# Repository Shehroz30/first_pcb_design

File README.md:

# first_pcb_design
my first pcb design with a stm32f1 microcontroller

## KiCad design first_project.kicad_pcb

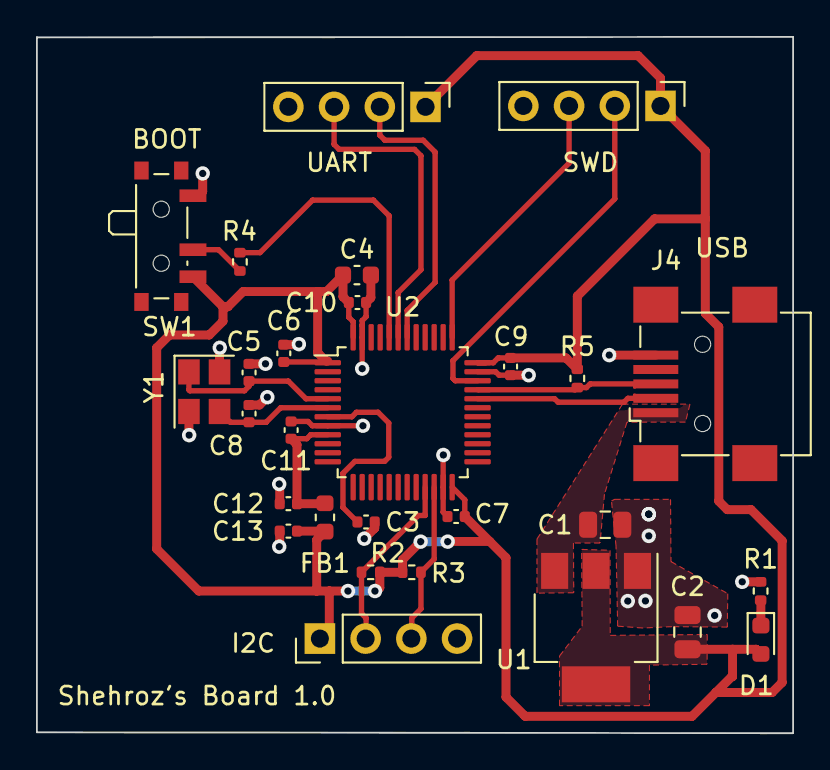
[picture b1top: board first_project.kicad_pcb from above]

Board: 2 copper layers, 42.0 x 38.7 mm, 28 parts (0 on the bottom side), 18 nets.

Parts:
C1, C2: 22u; C_0805_2012Metric
C3, C6, C7, C9, C10: 100n; C_0402_1005Metric
C4: 10u; C_0603_1608Metric
C5, C8: 10p; C_0402_1005Metric
C11: 10n; C_0402_1005Metric
C12, C13: 1u; C_0402_1005Metric
D1: RED; LED_0603_1608Metric
FB1: 120R; L_0603_1608Metric
J1, J2, J3: Conn_01x04_Male; PinHeader_1x04_P2.54mm_Vertical
J4: USB_B_Mini; USB_Mini-B_Wuerth_65100516121_Horizontal
R1, R2, R3, R5: 1k5; R_0402_1005Metric
R4: 10k; R_0402_1005Metric
SW1: SW_SPDT; SW_SPDT_PCM12
U1: AMS1117-3.3; SOT-223-3_TabPin2
U2: STM32F103C8T6; LQFP-48_7x7mm_P0.5mm
Y1: 16MHz; Crystal_SMD_3225-4Pin_3.2x2.5mm

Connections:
+3.3VA: C11.1, C12.1, FB1.2, U2.9
+3V3: C2.1, C4.1, C6.1, C7.1, C9.1, C10.1, C13.1, D1.2, FB1.1, J1.1, J2.1, J3.1, R2.1, R3.1, R5.1, SW1.3, U1.2, U2.1, U2.24, U2.36, U2.48
/HSE_IN: C5.1, U2.5, Y1.1
/HSE_OUT: C8.1, U2.6, Y1.3
/I2C2_SCL: J1.2, R2.2, U2.21
/I2C2_SDK: J1.3, R3.2, U2.22
/NRST: C3.1, U2.7
/SWCLK: J3.3, U2.37
/SWDIO: J3.2, U2.34
/USART1_RX: J2.3, U2.43
/USART1_TX: J2.2, U2.42
/USB_D+: J4.3, R5.2, U2.33
/USB_D-: J4.2, U2.32
GND: C1.2, C2.2, C3.2, C4.2, C5.2, C6.2, C7.2, C8.2, C9.2, C10.2, C11.2, C12.2, C13.2, J1.4, J2.4, J3.4, J4.5, R1.2, SW1.1, U1.1, U2.8, U2.23, U2.35, U2.47, Y1.2, Y1.4
unnamed: D1.1, R1.1
unnamed: R4.1, U2.44
unnamed: R4.2, SW1.2
VBUS: C1.1, J4.1, U1.3

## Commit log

2024-09-03 add bom
